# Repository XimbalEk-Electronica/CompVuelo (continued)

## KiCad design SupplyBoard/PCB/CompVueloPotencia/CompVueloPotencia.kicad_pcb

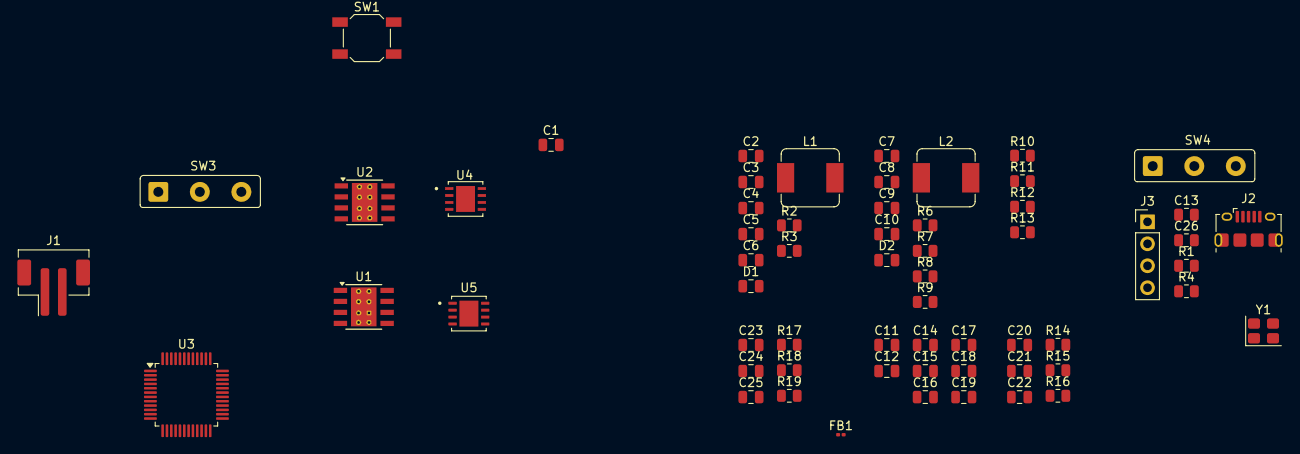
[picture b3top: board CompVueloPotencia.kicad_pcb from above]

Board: 2 copper layers, 61 parts (0 on the bottom side), 30 nets, no tracks yet.

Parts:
C1: .1uF; C_0805_2012Metric
C2, C3, C4, C7, C8: 47uF; C_0805_2012Metric
C5, C9: 10nF; C_0805_2012Metric
C6: 330uF; C_0805_2012Metric
C10: 560uF; C_0805_2012Metric
C11, C17, C20, C21, C23, C24: 10uF; C_0805_2012Metric
C12, C14, C15, C16: 100nF; C_0805_2012Metric
C13, C26: 9pF; R_0805_2012Metric
C18, C19: 1uF; C_0805_2012Metric
C22, C25: 470nF; C_0805_2012Metric
D1: 550mV; C_0805_2012Metric
D2: 450mV; C_0805_2012Metric
FB1: 10R@100MHz; L_0201_0603Metric
J1: Conn_01x02; JST_PH_B2B-PH-SM4-TB_1x02-1MP_P2.00mm_Vertical
J2: USB_B_Micro; USB_Micro-B_Amphenol_10118194_Horizontal
J3: ST_LINK; PinHeader_1x04_P2.54mm_Vertical
L1, L2: 10uH; L_Sumida_CDMC6D28_7.25x6.5mm
R1: 1k5; R_0805_2012Metric
R2, R4, R6: 10k; R_0805_2012Metric
R3: 3k; R_0805_2012Metric
R7: 4k7; R_0805_2012Metric
R8, R9: 330R; R_0805_2012Metric
R10, R13: 15k; R_0805_2012Metric
R11: 330k; R_0805_2012Metric
R12: 680k; R_0805_2012Metric
R14, R17: 33k; R_0805_2012Metric
R15, R18: 100k; R_0805_2012Metric
R16, R19: 39k; R_0805_2012Metric
SW1: Reset; SW_SPST_SKQG_WithStem
SW3: SW_SPDT_312; SolderWire-0.5sqmm_1x03_P4.8mm_D0.9mm_OD2.3mm
SW4: SW_SPDT; SolderWire-0.5sqmm_1x03_P4.8mm_D0.9mm_OD2.3mm
U1, U2: TPS5430DDA; TI_SO-PowerPAD-8_ThermalVias
U3: STM32F103CBT6; LQFP-48_7x7mm_P0.5mm
U4, U5: LD39200DPUR; SON80P400X400X100-9N
Y1: 16MHz; Crystal_SMD_3225-4Pin_3.2x2.5mm

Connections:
3V3_MCU: C11.1, C12.1, C14.1, C15.1, C16.1, C19.1, C24.1, C25.1, FB1.2, J3.1, R1.1, R18.1, SW4.2 (C), U3.1 (VBAT), U3.24 (VDD), U3.36 (VDD), U3.48 (VDD), U5.1 (OUT)
+7.4V: C7.1, C8.1, R11.1, SW3.2 (C), U2.7 (VIN)
+BATT: J1.2, SW3.1 (B)
/3V3_Outs/3V3_2: C21.1, C22.1, R15.1, U4.1 (OUT)
/3V3_Outs/LD39200_3v3_1/EN: C10.1, C20.1, C23.1, L2.2, R6.1, U4.6 (EN), U4.7 (IN), U5.6 (EN), U5.7 (IN)
/3V3_Outs/TPS5430_BuckConv_3.3V/EN: R10.1, R11.2, R13.1, U2.5 (EN)
/TPS5430_BuckConv_5V1/VIN: C2.1, C3.1, C4.1, U1.7 (VIN)
/TPS5430_BuckConv_5V1/VOUT: C6.1, L1.2, R2.1
BOOT0: R4.2, U3.44 (BOOT0)
GND: C1.2, C2.2, C3.2, C4.2, C6.2, C7.2, C8.2, C10.2, C11.2, C12.2, C13.2, C14.2, C15.2, C16.2, C17.2, C18.2, C19.2, C20.2, C21.2, C22.2, C23.2, C24.2, C25.2, C26.2, D1.2 (A), D2.2 (A), J1.1, J1.MP (MountPin), J2.5 (GND), J2.6 (Shield), J3.4, R3.2, R9.2, R12.2, R14.2, R16.2, R17.2, R19.2, SW1.1, SW4.3 (A), U1.6 (GND), U1.9 (GNDPAD), U2.6 (GND), U2.9 (GNDPAD), U3.8 (VSSA), U3.23 (VSS), U3.35 (VSS), U3.47 (VSS), U4.4 (GND), U4.9 (EXP), U5.4 (GND), U5.9 (EXP), Y1.2, Y1.4
NRST: C1.1, SW1.2, U3.7 (NRST)
unnamed: C5.2, D1.1 (K), L1.1, U1.8 (PH)
unnamed: C9.2, D2.1 (K), L2.1, U2.8 (PH)
unnamed: R7.2, R8.1
unnamed: R8.2, R9.1
unnamed: R10.2, R12.1, R13.2
unnamed: R4.1, SW4.1 (B)
unnamed: C5.1, U1.1 (BOOT)
unnamed: R2.2, R3.1, U1.4 (VSENSE)
unnamed: C9.1, U2.1 (BOOT)
unnamed: R6.2, R7.1, U2.4 (VSENSE)
unnamed: R14.1, R15.2, R16.1, U4.3 (ADJ)
unnamed: R17.1, R18.2, R19.1, U5.3 (ADJ)
OSC_IN: C26.1, U3.5 (PD0), Y1.1
OSC_OUT: C13.1, U3.6 (PD1), Y1.3
SWCLK: J3.3, U3.37 (PA14)
SWDIO: J3.2, U3.34 (PA13)
USB_D+: J2.3 (D+), R1.2, U3.33 (PA12)
USB_D-: J2.2 (D-), U3.32 (PA11)
VDDA: C17.1, C18.1, FB1.1, U3.9 (VDDA)

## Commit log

2025-08-24 añadir archivos kicad
2025-08-24 adding gitignore
2025-08-24 test for updates
2025-08-24 update ignore
2025-08-24 another test of updates
2025-08-24 last test for updates, only add to gitignore the prl file
2025-08-25 little changes
2025-08-25 del kicad_prl
2025-08-26 test from windows
2025-08-28 made the buck converter schematic & MCU selection
2025-09-02 uptade de schematic
2025-09-05 Actualizacion de esquematicos de fuente tipo Buck
2025-09-09 Semi finished the regulator-section
2025-09-09 update de distrubution
2025-09-09 Create LICENSE
2025-09-10 Mcu Finishes, i think
2025-09-10 modifying the gitignore
2025-09-12 Reorganize the folders in the project
2025-09-19 Supply Board - Remake Schematic in KiCad 9
2025-09-19 organize the folders
2025-09-19 Supply board - Update the current measurement
2025-09-19 supply board - delete backups
2025-09-22 SupplyBoard - finish current sense
    Finish the Current Sensor Circuit and add more 3.3V out, i change de microcontroles to a mcu that have the exact GPIO's
2025-09-22 Stop track backupfiles
2025-09-23 SupplyBoard - update layout
    schematic completed and PCB layout started; only the routing of the traces remains to be done
2025-09-25 Supply Board & Folder Organization
    Reorganization of the power supply board components, simplifying the layout to facilitate future debugging and reorganizing some folders and documents, as well as adding the power supply board schema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
2025-09-26 Start the S&CBoard
2025-10-03 Supply & Coms-Sensor Board
    la organizacion de los componentes presentes en las placas, se quedaran de esa manera, se espera que en la serigrafia se incluyan los logos de los patrocinadores, ademas se incluyo la carpeta 3D la c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
2025-10-07 C&S board - update GPS
    se cambio el conector del gps pasando de un sistema incorporado en placa a un sistema externo, con el BZ251
2025-10-08 C&S-board
    se avanzo en el trazado de pistas
2025-12-03 start a new version of the flight computer
2025-12-05 little changesss
2026-01-22 prueba0
    mostrar avance
